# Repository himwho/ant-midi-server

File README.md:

# Ant MIDI Server

A Node.js server that receives OSC messages from ant colony sensors and converts them to MIDI output, with real-time web interface and encryption capabilities.

## Features

- OSC to MIDI conversion
- Real-time web interface with Vue.js
- MIDI device selection and output
- Web Audio API synthesizer
- Security dashboard with hash generation
- File encryption using ant-generated entropy
- Socket.io real-time communication

## Installation

```bash
npm install
npm start
```

The server will start on port 3000 and listen for OSC messages on port 9998.

## Troubleshooting

### Common Issues

1. **"AntCrypt is not defined" error**
   - Make sure `public/js/encryption.js` is loaded before the main Vue app
   - Check browser console for script loading errors

2. **MIDI devices not showing**
   - Ensure browser supports Web MIDI API (Chrome/Edge recommended)
   - Check browser permissions for MIDI access
   - Look for MIDI access logs in browser console

3. **Socket.io connection errors (502)**
   - Check if server is running on correct port
   - Verify proxy/hosting configuration
   - Updated to socket.io v4.7.5 for better compatibility

4. **Vue template variables showing as `{{ }}`**
   - Indicates Vue.js failed to initialize
   - Check for JavaScript errors in console
   - Ensure all required scripts are loaded

5. **AudioContext warnings**
   - Modern browsers require user interaction before audio
   - Click on the page before using audio features
   - Consider using AudioWorkletNode instead of ScriptProcessorNode

### Development

- Main server: `main.js`
- Frontend: `index.html`
- Security dashboard: `security.html`
- Client scripts: `public/js/`

### File Structure

```
├── main.js              # Express server with Socket.io and OSC
├── index.html           # Main web interface
├── security.html        # Security dashboard
├── package.json         # Dependencies
└── public/
    ├── css/
    └── js/
        ├── encryption.js      # AntCrypt class for file encryption
        ├── midi.js           # MIDI handling
        ├── security-dashboard.js # Security hash generation
        ├── synth.js          # Web Audio synthesizer
        └── ui.js             # UI utilities
```

## API Endpoints

- `GET /` - Main dashboard
- `GET /security` - Security dashboard
- `GET /public/*` - Static assets

## Socket.io Events

- `osc` - OSC message data (x, y, z values)
- `internal` - Internal system data
- `hash` - Security hash updates

## OSC Integration

Send OSC messages to port 9998 with 3 float arguments:
- `/default` - General sensor data
- `/hash` - Security hash updates

## Components
 - C++ OpenFrameworks controller app for handling and broadcasting multiple ant colonie: [Controller Directory](desktop-controller)
 - Custom formicarium embedded with various sensors (first generations focused on LDRs): [CAD Design Directory](custom-formicarium/cad/antformicarium-assembled)
 - Circuit for handling sensors, circuit allows analog -5v->+5v CV output as well as shield mounting for Arduino Uno form factor boards: [Circuit Design Directory](custom-formicarium/circuit-design/)
 - C Controller code for digital ADV handling for the sensors: [Arduino Controller Code](arduino-controller/ant-arduino-6i-controller.ino)
 - (Temporary) Max patch for receiving all arduino controllers and pushing them forward as OSC for web component: [Max Patch Controller](max-controller/AntPlayer.maxpat)
 - NodeJS handler receiving OSC on LAN and pushing socket.io as an OSC stream
 - Client side static website receving stream and outputting MIDI for any local device

## Usage
Server listens for messages via OSC and sends them to any connecting client via HTTP

## TODO List
- parse seperate input devices for multichannel MIDI
- stylize the web component
- cleanup the max patch
- design arduino patch to output OSC directly
- workout a feedback design for audio to vibrate safely the colony enclosures

## Notes
Moving OSC handling to arduino controller side may be an issue due to lack of multithreading already for parsing sensors

usbmodem14601 = hab001 = Brown Camponotus P. Hab
usbmodem1434301 = hab002 = Clear Camponotus P. Hab
usbmodem = hab003 = Tan Camponotus P. Hab

## Ant Journal
I originally chose ants for this thinking they would be easy to handle and grow into large numbers making them ideal for entropy and synthesizing perceived randomness. It turns out its very challenging to get a queen ant to properly pass the foundling stage and grow into a sustaining colony. Below will be some notes and issues I did not expect more specific to this project.

#### Light Sesnsitivity
Using LDR (light) based sensors is not ideal, queen ants tend to get stressed out from light, part of the project included training the queen ant(s) to get used to light to keep this project running longer term. Queen ants that did not have a light cover showed at least a 50% decrease in colony size over time. I only started light training for a colony when they got to a certain size (generally over 15 workers).

#### Colony Growth
I picked Camponotus Pennsylvanicus because they were common and enormous. However I did not realize this species of ant is slower to grow in colony size, I originally expected an ant colony to take weeks at most, but this extended the project to a 2-3 year timeline.

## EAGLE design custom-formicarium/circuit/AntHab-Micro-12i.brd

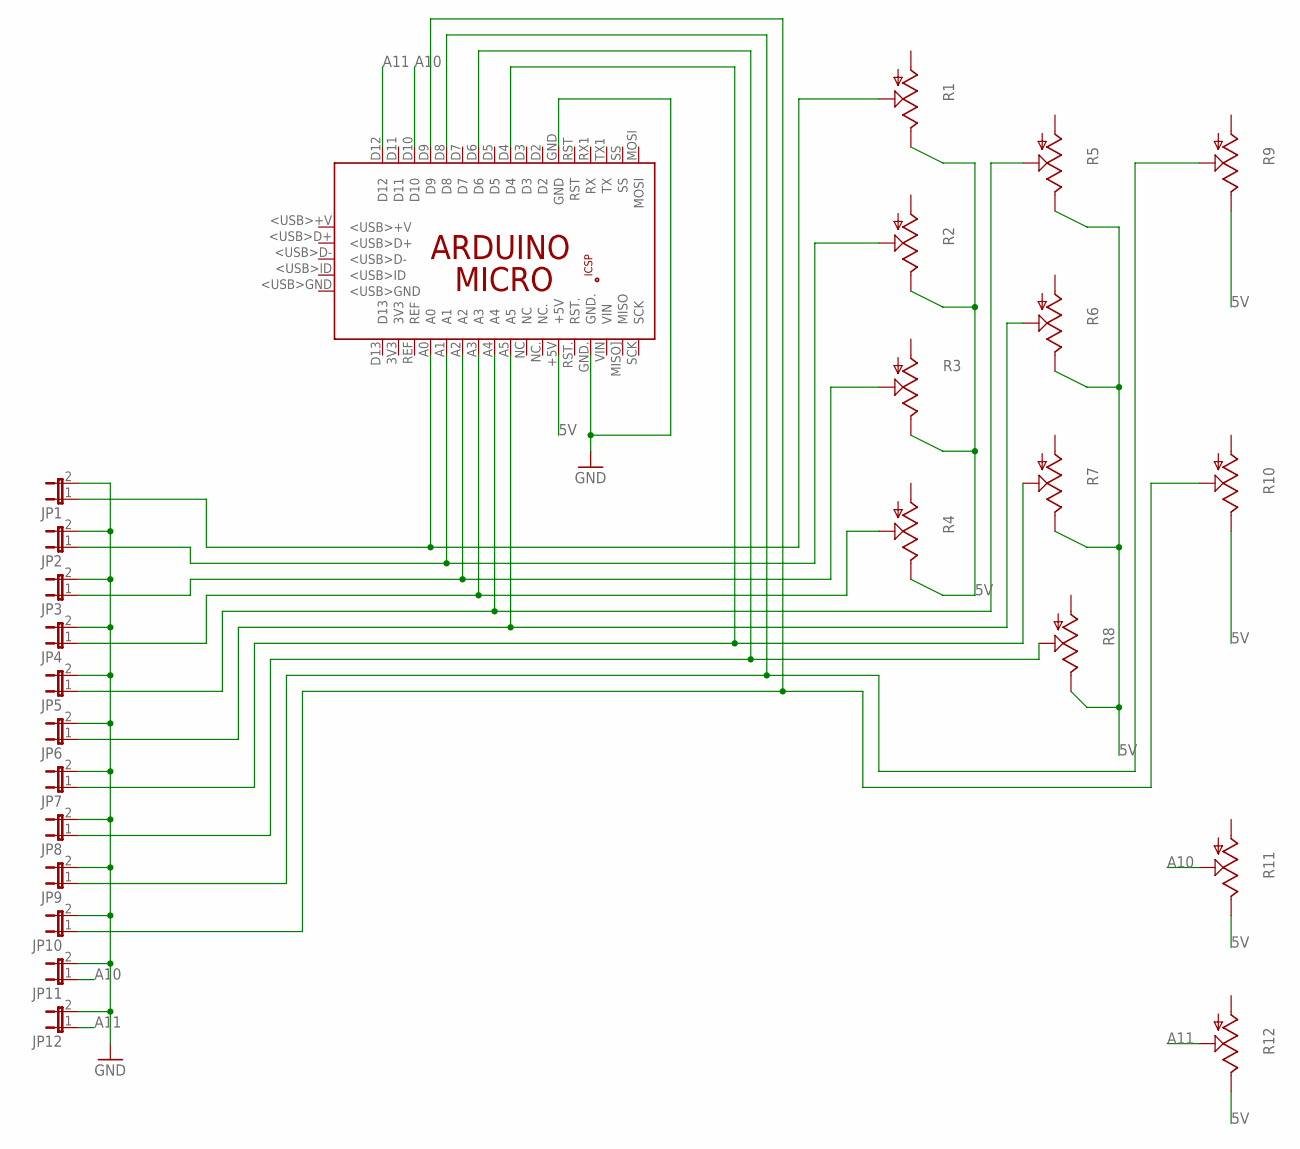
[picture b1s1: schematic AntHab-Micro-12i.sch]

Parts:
JP1, JP2, JP3, JP4, JP5, JP6, JP7, JP8, JP9, JP10, JP11, JP12: JP1E; JP1
PCB1: ARDUINO_MICRO
R1, R2, R3, R4, R5, R6, R7, R8, R9, R10, R11, R12: TRIM_US-CT6; CT6

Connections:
5V: PCB1.+5V, R1.E, R2.E, R3.E, R4.E, R5.E, R6.E, R7.E, R8.E, R9.E, R10.E, R11.E, R12.E
A10: JP11.1, PCB1.D10, R11.S
A11: JP12.1, PCB1.D12, R12.S
GND: JP1.2, JP2.2, JP3.2, JP4.2, JP5.2, JP6.2, JP7.2, JP8.2, JP9.2, JP10.2, JP11.2, JP12.2, PCB1.GND, PCB1.GND.
unnamed: JP4.1, PCB1.A3, R4.S
unnamed: JP5.1, PCB1.A4, R5.S
unnamed: JP6.1, PCB1.A5, R6.S
unnamed: JP7.1, PCB1.D4, R7.S
unnamed: JP8.1, PCB1.D6, R8.S
unnamed: JP9.1, PCB1.D8, R9.S
unnamed: JP10.1, PCB1.D9, R10.S
unnamed: JP1.1, PCB1.A0, R1.S
unnamed: JP2.1, PCB1.A1, R2.S
unnamed: JP3.1, PCB1.A2, R3.S

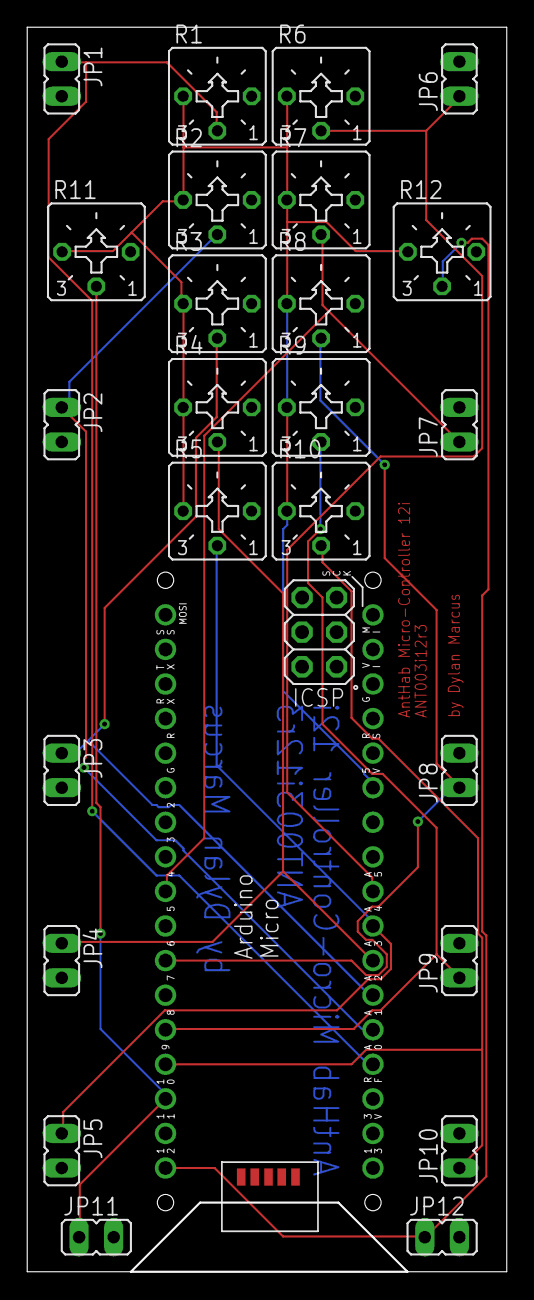
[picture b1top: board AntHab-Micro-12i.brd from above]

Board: 2 copper layers, 35.1 x 91.4 mm, 25 parts (0 on the bottom side), 14 nets.

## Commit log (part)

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2019-07-12 init for dockerization
2019-07-12 init for webmidi
2019-07-14 switched to jazz midi test
2019-08-14 added static html midi page that inputs midi
2019-08-14 cleanup round 2
2019-08-15 added midi output, and added displayed input notes
2019-08-18 working udp receive and parse of OSC
2019-08-18 nodejs pulls in public files, removed doubled files
2019-08-18 more cleanup and styles
2019-08-19 opened new socket for internal midi feedback to client
2019-08-19 more styling
2019-08-19 primitive autoscroller
2020-06-07 added init for max controller, arduino controller and design for cad enclosure
2020-06-07 added new 6i to osc handling
2020-06-07 removed old ino, update hab for testing
2020-06-08 added new dev collector max patch and remade the arduino patches for simplicity
2020-06-08 updated max patch
2020-06-08 added to maxpatch
2020-07-12 DesktopController: init
2020-07-13 arduino: updated arduino's for call and response
2020-07-13 DesktopController: fixed the frame issue, and separate connections fixed
2020-07-13 DesktopController: minor changes
2020-07-17 DesktopController: minor updates for processing
2020-07-18 DesktopController: fixed paths and added some more parsing
2020-07-19 DesktopController: WIP for adding processing
2020-07-21 DekstopController: more parsing to osc
2020-07-21 DesktopController: added some resizing handling
2020-07-25 DekstopController: stabilize vector handling
2020-07-26 DesktopController: working init for end to end transmission by fixing the output osc message
2020-07-26 DesktopController: addon for midi messages
2020-08-01 DesktopController: WIP for a few checks on startup
2020-08-02 DesktopController: some updates for handling
2020-08-02 DesktopController: fully fixed flow and initialization
2020-08-02 DesktopController: removed some debug and cleanup
2020-08-03 DesktopController: init for multithreading
2020-08-04 DesktopController: attempt at destroying finished osc notes
2020-08-04 DesktopController: add thread counter
2020-08-04 DesktopController: added exit function
2020-08-04 DesktopController: changed triggers to have each device use different midi channel, moved the video to be background
2020-08-04 DesktopController: init for security seed sending via udp
2020-08-04 readme: updated
2020-08-04 DesktopController: better port handling
2020-08-04 js: can now parse a second UDP connection for security seed
2020-08-04 js: working int parsed seed on client side
2020-08-08 DesktopController: side test of FDL
2020-08-08 DesktopController: readability improvement
2020-08-12 DesktopController: handling multiple videos
2020-08-13 DesktopController: safeguard for drawing camera feeds, init for transmitting images via OSC
2020-08-18 DesktopController: updated video socket send
2020-08-20 DesktopController: init for better debug control
2020-08-20 DesktopController: added trigger vars and a setup run blocker
2020-08-21 DesktopController: temp logging
2020-08-22 DesktopController: fixed tab and file
2020-08-23 DesktopController: write bugfix
2020-08-25 DesktopController: refactored logging
2020-08-25 DesktopController: macro fixed and some cleanup
2020-08-26 DesktopController: minor fixes
2020-08-28 DesktopController: minor bugfix
2020-09-02 DesktopController: custom constructor for videos
2020-09-28 add vue frontend
2020-09-28 some html cleanup
2020-09-28 shouldnt have to specify host when in prod
2020-09-30 add controls for web synth
2021-01-18 data-reader: init for log parsing python scripts
2021-01-20 data-reader: init for jupyter notebook
2021-01-21 Bump socket.io from 2.2.0 to 2.4.0
    Bumps [socket.io](https://github.com/socketio/socket.io) from 2.2.0 to 2.4.0.
    - [Release notes](https://github.com/socketio/socket.io/releases)
    - [Changelog](https://github.com/socketio/socket.io/blob/2.4.0/CHANGELOG.md)
    - [Commits](https://github.com/socketio/socket.io/compare/2.2.0...2.4.0)
2021-05-01 firmware: added 10input firmware
2021-05-05 firmware/controller: firmware slowed down, introduced max number of OSC threads on controller
2021-05-10 desktop-controller: start for adding multiple trigger threshold amounts per device
2021-07-19 firmware: updated ino files slightly for better SRAM handling
2021-07-19 desktop-controller: fixed bug blocking draw flow, but introduces new bug (slow loop bug)
2021-07-22 desktop-controller: some flow improvements
2021-07-23 desktop-controller: reduced screen size and attempted to fix write flow logic
2021-07-23 desktop-controller: added a serial flush
2021-07-23 desktop-controller: fixed flow issues
2021-08-16 firmware: improved loop for 6i firmware
2022-03-01 desktop-controller: init for new hd cam handling for cv
2022-03-01 desktop-controller: added baked xcodeproj for tracking
2022-03-14 desktop-controller: init for flow detection tests
2022-03-15 desktop-controller: wip for farneback processing
2022-03-15 desktop-controller: cv added with diff to blur to contourfinder flow
2022-06-03 desktop-controller: added debug for cv to osc
2022-10-30 Bump socket.io-parser from 3.3.0 to 3.4.1
    Bumps [socket.io-parser](https://github.com/socketio/socket.io-parser) from 3.3.0 to 3.4.1.
    - [Release notes](https://github.com/socketio/socket.io-parser/releases)
    - [Changelog](https://github.com/socketio/socket.io-parser/blob/main/CHANGELOG.md)
    - [Commits](https://github.com/socketio/socket.io-parser/compare/3.3.0...3.4.1)
    ---
    updated-dependencies:
2022-11-12 Bump socket.io-parser from 3.3.0 to 3.4.2
    Bumps [socket.io-parser](https://github.com/socketio/socket.io-parser) from 3.3.0 to 3.4.2.
    - [Release notes](https://github.com/socketio/socket.io-parser/releases)
    - [Changelog](https://github.com/socketio/socket.io-parser/blob/main/CHANGELOG.md)
    - [Commits](https://github.com/socketio/socket.io-parser/compare/3.3.0...3.4.2)
    ---
    updated-dependencies:
2022-12-06 Bump qs and express
    Bumps [qs](https://github.com/ljharb/qs) to 6.11.0 and updates ancestor dependency [express](https://github.com/expressjs/express). These dependencies need to be updated together.
    Updates `qs` from 6.7.0 to 6.11.0
    - [Release notes](https://github.com/ljharb/qs/releases)
    - [Changelog](https://github.com/ljharb/qs/blob/main/CHANGELOG.md)
    - [Commits](https://github.com/ljharb/qs/compare/v6.7.0...v6.11.0)
    Updates `express` from 4.17.1 to 4.18.2
2022-12-10 Bump express from 4.17.1 to 4.17.3
    Bumps [express](https://github.com/expressjs/express) from 4.17.1 to 4.17.3.
    - [Release notes](https://github.com/expressjs/express/releases)
    - [Changelog](https://github.com/expressjs/express/blob/master/History.md)
    - [Commits](https://github.com/expressjs/express/compare/4.17.1...4.17.3)
    ---
    updated-dependencies:
2023-07-18 update the cv->midi algo
2023-07-19 updated gitignore for data
2023-08-20 updated the debug view flags
2023-08-20 some more improvements to sending notes, fixed the player deletion loop
2023-08-20 fixed issue incorrectly parsing min/max values due to using floats on expected ints
2023-12-13 add inlay stream to web browser page
2024-02-15 init for the hashing idea
2024-02-15 add more parent types for the twitch ancestors
2024-03-29 Bump express from 4.18.2 to 4.19.2
    Bumps [express](https://github.com/expressjs/express) from 4.18.2 to 4.19.2.
    - [Release notes](https://github.com/expressjs/express/releases)
    - [Changelog](https://github.com/expressjs/express/blob/master/History.md)
    - [Commits](https://github.com/expressjs/express/compare/4.18.2...4.19.2)
    ---
    updated-dependencies:
2025-05-27 more hash updates
2025-05-27 moved some elements
2025-05-27 remove front page encrypt
2025-05-27 remove encrypt from index
2025-05-27 Bump cookie, express and socket.io
    Bumps [cookie](https://github.com/jshttp/cookie) to 0.7.1 and updates ancestor dependencies [cookie](https://github.com/jshttp/cookie), [express](https://github.com/expressjs/express) and [socket.io]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
    Updates `cookie` from 0.6.0 to 0.7.1
    - [Release notes](https://github.com/jshttp/cookie/releases)
    - [Commits](https://github.com/jshttp/cookie/compare/v0.6.0...v0.7.1)
    Updates `express` from 4.19.2 to 4.21.2
    - [Release notes](https://github.com/expressjs/express/releases)
2025-05-27 Bump body-parser and express
    Bumps [body-parser](https://github.com/expressjs/body-parser) to 1.20.3 and updates ancestor dependency [express](https://github.com/expressjs/express). These dependencies need to be updated together.
    Updates `body-parser` from 1.20.2 to 1.20.3
    - [Release notes](https://github.com/expressjs/body-parser/releases)
    - [Changelog](https://github.com/expressjs/body-parser/blob/master/HISTORY.md)
    - [Commits](https://github.com/expressjs/body-parser/compare/1.20.2...1.20.3)
    Updates `express` from 4.19.2 to 4.21.2
2025-05-27 Bump send and express
    Bumps [send](https://github.com/pillarjs/send) to 0.19.0 and updates ancestor dependency [express](https://github.com/expressjs/express). These dependencies need to be updated together.
    Updates `send` from 0.18.0 to 0.19.0
    - [Release notes](https://github.com/pillarjs/send/releases)
    - [Changelog](https://github.com/pillarjs/send/blob/master/HISTORY.md)
    - [Commits](https://github.com/pillarjs/send/compare/0.18.0...0.19.0)
    Updates `express` from 4.19.2 to 4.21.2
2025-05-27 Bump socket.io-parser from 3.3.3 to 4.2.4
    Bumps [socket.io-parser](https://github.com/Automattic/socket.io-parser) from 3.3.3 to 4.2.4.
    - [Release notes](https://github.com/Automattic/socket.io-parser/releases)
    - [Changelog](https://github.com/socketio/socket.io-parser/blob/4.2.4/CHANGELOG.md)
    - [Commits](https://github.com/Automattic/socket.io-parser/compare/3.3.3...4.2.4)
    ---
    updated-dependencies:
2025-05-28 improved encryption portal
2025-05-28 Bump path-to-regexp and express
    Bumps [path-to-regexp](https://github.com/pillarjs/path-to-regexp) to 0.1.12 and updates ancestor dependency [express](https://github.com/expressjs/express). These dependencies need to be updated tog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
    Updates `path-to-regexp` from 0.1.7 to 0.1.12
    - [Release notes](https://github.com/pillarjs/path-to-regexp/releases)
    - [Changelog](https://github.com/pillarjs/path-to-regexp/blob/master/History.md)
    - [Commits](https://github.com/pillarjs/path-to-regexp/compare/v0.1.7...v0.1.12)
    Updates `express` from 4.19.2 to 4.21.2
2025-05-28 Bump express from 4.19.2 to 4.20.0
    Bumps [express](https://github.com/expressjs/express) from 4.19.2 to 4.20.0.
    - [Release notes](https://github.com/expressjs/express/releases)
    - [Changelog](https://github.com/expressjs/express/blob/master/History.md)
    - [Commits](https://github.com/expressjs/express/compare/4.19.2...4.20.0)
    ---
    updated-dependencies:
2025-05-28 fixed decryption
2025-05-28 update public
2025-05-30 setup relay mode
2025-06-15 console logging enabled
2025-06-15 fixed missing history bug on log
2025-06-15 style change for main page
2025-11-25 Bump body-parser and express
    Bumps [body-parser](https://github.com/expressjs/body-parser) to 2.2.1 and updates ancestor dependency [express](https://github.com/expressjs/express). These dependencies need to be updated together.
    Updates `body-parser` from 1.20.2 to 2.2.1
    - [Release notes](https://github.com/expressjs/body-parser/releases)
    - [Changelog](https://github.com/expressjs/body-parser/blob/master/HISTORY.md)
    - [Commits](https://github.com/expressjs/body-parser/compare/1.20.2...v2.2.1)
    Updates `express` from 4.19.2 to 5.1.0
2025-12-30 Bump qs and express
    Bumps [qs](https://github.com/ljharb/qs) to 6.14.1 and updates ancestor dependency [express](https://github.com/expressjs/express). These dependencies need to be updated together.
    Updates `qs` from 6.11.0 to 6.14.1
    - [Changelog](https://github.com/ljharb/qs/blob/main/CHANGELOG.md)
    - [Commits](https://github.com/ljharb/qs/compare/v6.11.0...v6.14.1)
    Updates `express` from 4.19.2 to 4.22.1
    - [Release notes](https://github.com/expressjs/express/releases)
